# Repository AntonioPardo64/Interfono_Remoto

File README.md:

# Interfono_Remoto
Proyecto Interfono Remoto (TFG)

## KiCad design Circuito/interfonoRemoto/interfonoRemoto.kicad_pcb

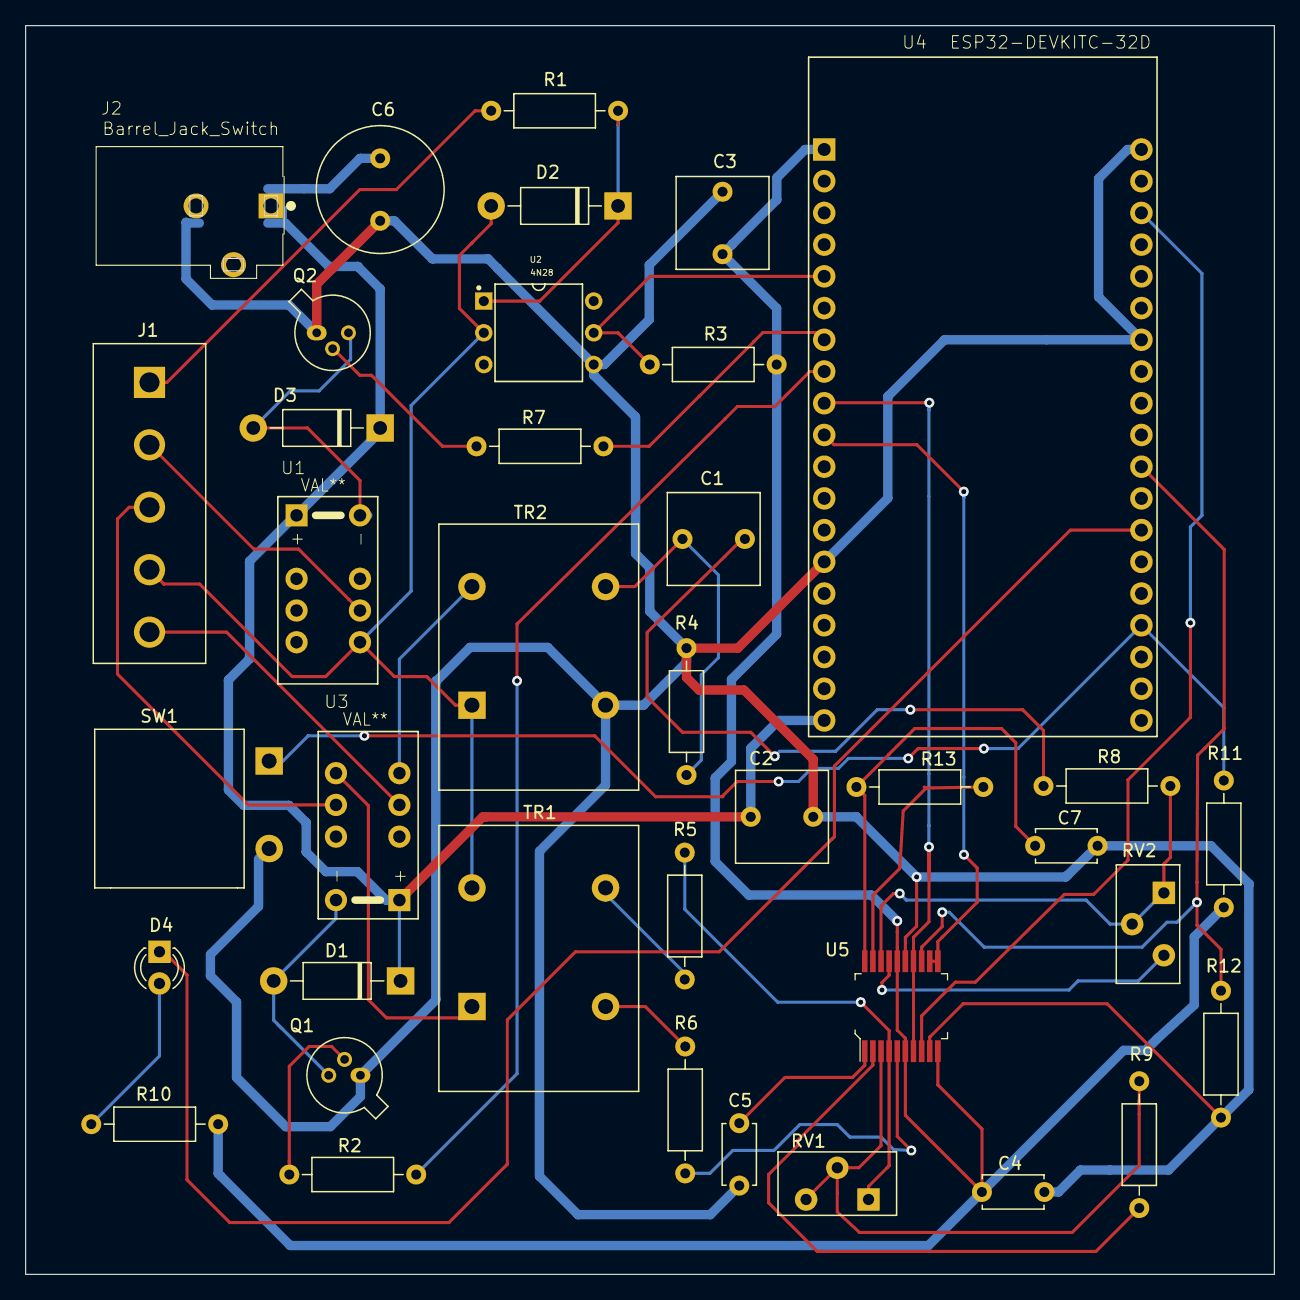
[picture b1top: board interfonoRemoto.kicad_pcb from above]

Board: 2 copper layers, 100.0 x 100.0 mm, 38 parts (0 on the bottom side), 38 nets.

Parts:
C1, C2, C3: 1uF; C_Rect_L7.2mm_W7.2mm_P5.00mm_FKS2_FKP2_MKS2_MKP2
C4, C5: 100nF; C_Disc_D4.7mm_W2.5mm_P5.00mm
C6: 10uF; C_Radial_D10.0mm_H16.0mm_P5.00mm
C7: 10nF; C_Disc_D4.7mm_W2.5mm_P5.00mm
D1, D2, D3: 1N4001; D_DO-41_SOD81_P10.16mm_Horizontal
D4: LED; LED_D3.0mm
J1: Screw_Terminal_01x05; conector_YO0521500000G
J2: Barrel_Jack_Switch; CUI_PJ-102A
Q1, Q2: BC107; TO-18-3
R1: 470R; R_Axial_DIN0207_L6.3mm_D2.5mm_P10.16mm_Horizontal
R2, R3, R7, R11: 1K2; R_Axial_DIN0207_L6.3mm_D2.5mm_P10.16mm_Horizontal
R4: 600R; R_Axial_DIN0207_L6.3mm_D2.5mm_P10.16mm_Horizontal
R5, R6: 0R; R_Axial_DIN0207_L6.3mm_D2.5mm_P10.16mm_Horizontal
R8, R9, R13: 4K7; R_Axial_DIN0207_L6.3mm_D2.5mm_P10.16mm_Horizontal
R10: 220R; R_Axial_DIN0207_L6.3mm_D2.5mm_P10.16mm_Horizontal
R12: 3K3; R_Axial_DIN0207_L6.3mm_D2.5mm_P10.16mm_Horizontal
RV1, RV2: 10K; Potenciometro
SW1: SW_Push; pulsador_Judco_50-0015-00
TR1, TR2: ADT1-1; Transformador_Tamura_TTC-105
U1, U3: VAL**; EC2-5NU
U2: 4N28; Optoacoplador_DIP880W50P254L780H450Q6
U4: ESP32-DEVKITC-32D; MODULE_ESP32-DEVKITC-32D
U5: w681360; SSOP-20_W5.3mm

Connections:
+3V3: C3.1, C4.1, R3.2, R10.1, R11.2, U4.1, U5.6, U5.10, U5.16
+5V: C2.1, C6.1, D1.1, D3.1, J2.1, U1.1, U3.1, U4.19
AI-: R8.1, RV2.1, RV2.2, U5.18
Auricular: J1.5, U3.4
Comun: D2.2, J1.4, TR1.3, TR2.1, U1.8, U2.2
Descolgar: R2.1, U4.8
FSR: U4.9, U5.7, U5.14
GND: C2.2, C3.2, C4.2, C5.1, C6.2, C7.1, J2.2, Q1.1, Q2.1, R4.1, R12.2, SW1.2, TR2.6, U2.4, U4.14, U4.20, U4.26, U5.9, U5.15
MCLK: U4.10, U5.11, U5.12
Microfono: J1.3, U3.9
unnamed: C1.1, R8.2
unnamed: C1.2, R4.2, TR2.4
unnamed: C5.2, U5.1
unnamed: C7.2, R13.1, U5.20
unnamed: D1.2, Q1.3, U3.12
unnamed: D2.1, R1.1, U2.1
unnamed: D3.2, Q2.3, U1.12
unnamed: D4.1, U4.32
unnamed: D4.2, R10.2
unnamed: J1.1, R1.2
unnamed: J1.2, U1.9
unnamed: Q1.2, R2.2
unnamed: Q2.2, R7.2
unnamed: R5.1, TR1.4
unnamed: R6.1, TR1.6
unnamed: R9.1, U5.2
unnamed: R9.2, RV1.2, RV1.3, U5.3
unnamed: R11.1, SW1.1, U4.35
unnamed: R13.2, U5.19
unnamed: RV2.3, U5.17
unnamed: TR1.1, U3.8
unnamed: TR2.3, U3.5
PAO+: R6.2, U5.5
PAO-: R5.2, RV1.1, U5.4
PCMR: U4.22, U5.8
PCMT: R12.1, U4.30, U5.13
Puerta: R7.1, U4.7
Timbre: R3.1, U2.5, U4.5

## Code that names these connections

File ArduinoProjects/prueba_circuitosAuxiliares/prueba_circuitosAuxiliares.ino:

#define PIN_BOTON 15
#define PIN_TMBR 34    	// pin del esp32 conectado al timbre
#define PIN_DCOL 33    	// pin del esp32 conectado a descolgar
#define PIN_PUER 32   	// pin del esp32 conectado a la puerta 
#define PIN_LED 4    	// pin del esp32 conectado al led


void iniPin(){
	pinMode(PIN_TMBR,INPUT);	// timbre
	pinMode(PIN_BOTON,INPUT); 	// botón
	pinMode(PIN_DCOL,OUTPUT);	// descolgar 
	pinMode(PIN_PUER,OUTPUT);	// puerta
	pinMode(PIN_LED,OUTPUT);	// LED
}

void setup() {
  Serial.begin(115200);
	iniPin();
  Serial.println("Iniciado..");
}


void loop() {
  
	if(!digitalRead(PIN_BOTON))
	{
		if(!digitalRead(PIN_TMBR)) {
			digitalWrite(PIN_DCOL,HIGH);
			digitalWrite(PIN_PUER,LOW);
			digitalWrite(PIN_LED,LOW);
		} else {
			digitalWrite(PIN_DCOL,LOW);
			digitalWrite(PIN_PUER,HIGH);
			digitalWrite(PIN_LED,HIGH);
		}
	} else {
		digitalWrite(PIN_DCOL,LOW);
		digitalWrite(PIN_PUER,LOW);
		digitalWrite(PIN_LED,LOW);
	}
}

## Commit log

2020-07-18 Version Inicial.
2020-07-20 Senalizacion de timbre.
